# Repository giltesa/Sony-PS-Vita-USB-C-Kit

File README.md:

# Sony PS Vita USB-C Kit

The **Sony PS Vita: USB-C Kit** is a board that allows to replace the original charging connector for a modern and standard **USB-C**.

**If your original connector is too old or damaged** and you need a new one, or **if you would like to charge your Sony PS Vita with a standard USB-C charger**, like the charger of your phone, laptop, you can with this board.

This board is compatible with this model:

*   Sony PS Vita

## Would you like it?

https://shop.giltesa.com/product/sony-ps-vita-usb-c-kit/

## More

- [giltesa.com](https://giltesa.com "giltesa.com")
- [twitter.com](https://twitter.com/giltesa "twitter.com")

## License

This project is licensed under a **Creative Commons** license:
**[Attribution-NonCommercial-ShareAlike 4.0 International (CC BY-NC-SA 4.0) ](https://creativecommons.org/licenses/by-nc-sa/4.0/)**

Check the [LICENSE.md](LICENSE.md) for more information.

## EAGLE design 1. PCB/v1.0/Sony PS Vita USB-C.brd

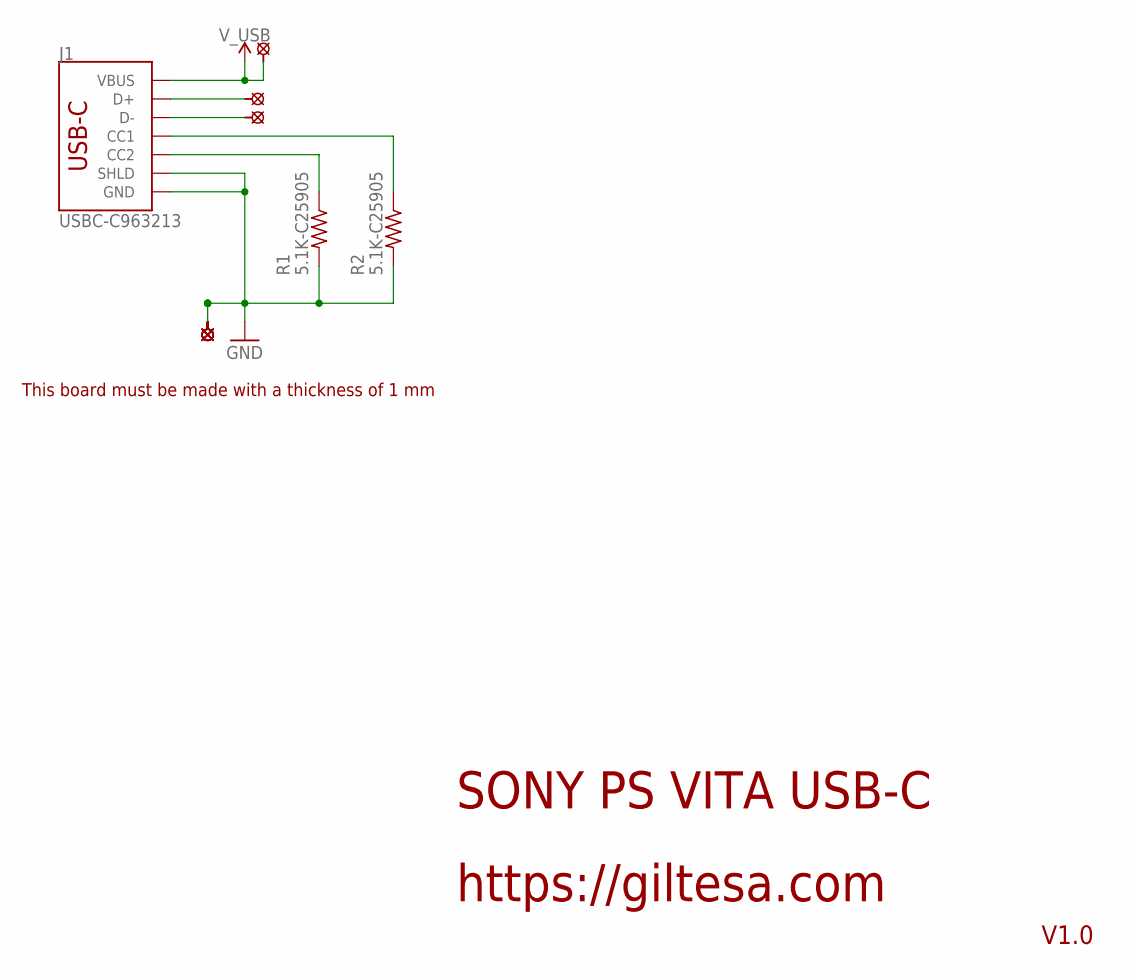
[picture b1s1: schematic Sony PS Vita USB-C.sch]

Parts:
J1: USBC-C963213; USB-C_18P_SLIM_GT-USB-7025
R1, R2: 5.1K-C25905; R0402
U$3, U$5, U$6: SOLDER_PAD-1.5; SOLDER_PAD_1.5
U$4, U$7, U$8, U$9: PAD_1.0

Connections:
CC1: J1.A5-CC1 (CC1), R2.1
CC2: J1.B5-CC2 (CC2), R1.1
D+: J1.A6-DP1 (D+), J1.B6-DP2 (D+), U$5.P$1
D-: J1.A7-DN1 (D-), J1.B7-DN2 (D-), U$6.P$1
GND: J1.A1-GND (GND), J1.A12-GND (GND), J1.B1-GND (GND), J1.B12-GND (GND), J1.GND1 (GND), J1.GND2 (GND), J1.SHLD1 (SHLD), J1.SHLD2 (SHLD), J1.SHLD3 (SHLD), J1.SHLD4 (SHLD), R1.2, R2.2, U$4.P$1, U$7.P$1, U$8.P$1, U$9.P$1
V_USB: J1.A4-VBUS (VBUS), J1.A9-VBUS (VBUS), J1.B4-VBUS (VBUS), J1.B9-VBUS (VBUS), U$3.P$1

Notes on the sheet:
SONY PS VITA USB-C
https://giltesa.com
V1.0
This board must be made with a thickness of 1 mm

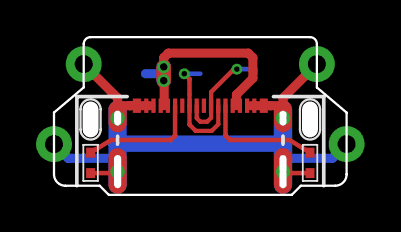
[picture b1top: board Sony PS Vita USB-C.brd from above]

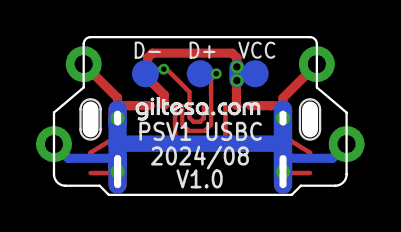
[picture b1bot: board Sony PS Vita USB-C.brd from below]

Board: 2 copper layers, 16.3 x 8.8 mm, 13 parts (4 on the bottom side), 6 nets.

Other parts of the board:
U$1, U$10: PS_VITA_HOLE
U$11: GILTESA.COM_MASK_7MM

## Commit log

2024-07-24 no message
2025-03-06 v1.0

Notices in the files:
parts and their libraries:
SparkFun: Licensing: CC v3.0 Share-Alike You are welcome to use this library for commercial purposes.
SparkFun-PowerSymbols: Licensing: Creative Commons ShareAlike 4.0 International - https://creativecommons.org/licenses/by-sa/4.0
